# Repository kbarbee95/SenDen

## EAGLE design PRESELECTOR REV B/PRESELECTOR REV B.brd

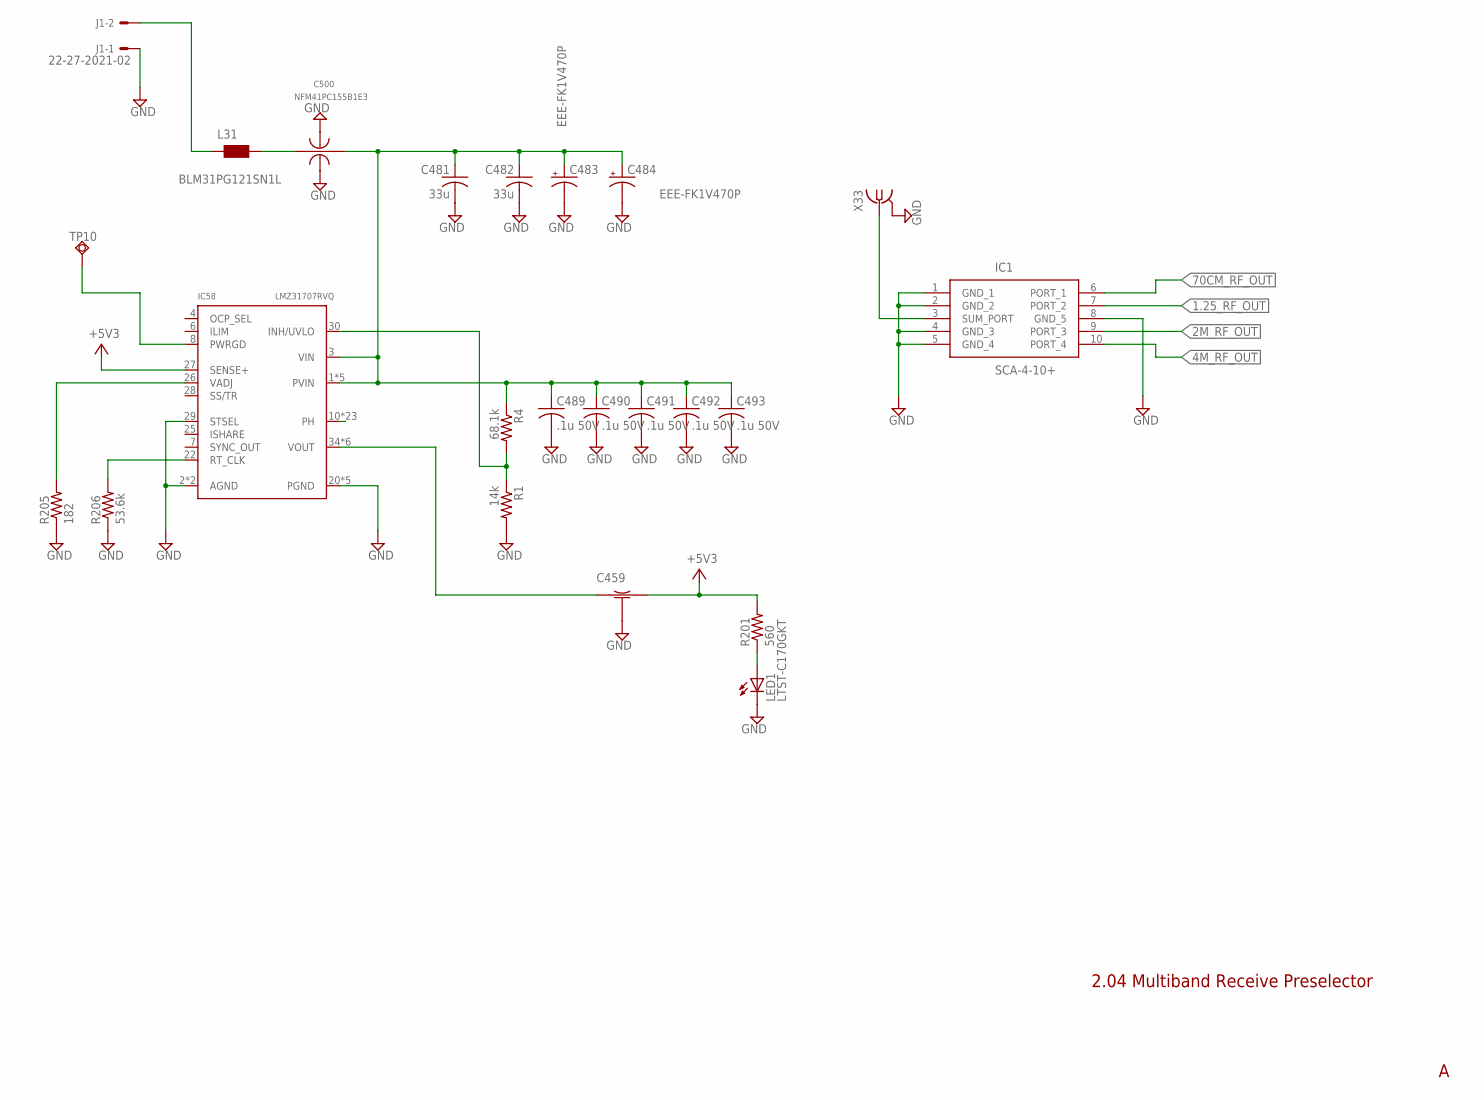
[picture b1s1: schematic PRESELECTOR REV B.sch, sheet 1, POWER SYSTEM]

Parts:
C459: NFM31PC276B0J3L; NFM31PC276
C481, C482: 33u; C1206K
C483, C484: EEE-FK1V470P; PANASONIC_D
C489, C490, C491, C492, C493: .1u 50V; C0603K
C500: NFM41PC155B1E3; NFM1806
IC1: SCA-4-10+
IC58: LMZ31707RVQ; RVQ
J1: 22-27-2021-02; 6410-02
L31: BLM31PG121SN1L; 1206
LED1: LTST-C170GKT; CHIPLED_0805
R1: 14k; R0603
R4: 68.1k; R0603
R201: 560; R0603
R205: 182; R0603
R206: 53.6k; R0603
TP10: TPSQB1,27; B1,27
X33: 0733660061; BU-SMA-V

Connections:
1.25_RF_OUT: IC1.7 (PORT_2); also elsewhere on the board
2M_RF_OUT: IC1.9 (PORT_3); also elsewhere on the board
4M_RF_OUT: IC1.10 (PORT_4); also elsewhere on the board
70CM_RF_OUT: IC1.6 (PORT_1); also elsewhere on the board
+5V3: C459.OUT, IC58.27 (SENSE+), R201.2; also elsewhere on the board
+13.8V_SW_FIL: C481.1, C482.1, C483.+, C484.+, C489.1, C490.1, C491.1, C492.1, C493.1, C500.2 (OUT), IC58.1 (PVIN), IC58.3 (VIN), IC58.11 (PVIN), IC58.12 (PVIN), IC58.39 (PVIN), IC58.40 (PVIN), R4.1
+13.8V_TPS: J1.2, L31.1
GND: C459.GND1 (GND), C459.GND2 (GND), C459.GND3 (GND), C459.GND4 (GND), C459.GND5 (GND), C481.2, C482.2, C483.-, C484.-, C489.2, C490.2, C491.2, C492.2, C493.2, C500.GND@1 (GND), C500.GND@2 (GND), IC1.1 (GND_1), IC1.2 (GND_2), IC1.4 (GND_3), IC1.5 (GND_4), IC1.8 (GND_5), IC58.2 (AGND), IC58.20 (PGND), IC58.21 (PGND), IC58.23 (AGND), IC58.29 (STSEL), IC58.31 (PGND), IC58.32 (PGND), IC58.33 (PGND), J1.1, LED1.C, R1.2, R205.1, R206.1, X33.2 (GND), X33.3 (GND), X33.4 (GND), X33.5 (GND); also elsewhere on the board
unnamed: C500.1 (IN), L31.2
unnamed: IC58.30 (INH/UVLO), R1.1, R4.2
unnamed: IC58.8 (PWRGD), TP10.TP
unnamed: IC58.22 (RT_CLK), R206.2
unnamed: IC58.26 (VADJ), R205.2
unnamed: C459.IN, IC58.34 (VOUT), IC58.35 (VOUT), IC58.36 (VOUT), IC58.37 (VOUT), IC58.38 (VOUT), IC58.41 (VOUT)
unnamed: LED1.A, R201.1
PH: IC58.10 (PH), IC58.13 (PH), IC58.14 (PH), IC58.15 (PH), IC58.16 (PH), IC58.17 (PH), IC58.18 (PH), IC58.19 (PH), IC58.42 (PH), IC58.42A (PH), IC58.42B (PH), IC58.42C (PH), IC58.42D (PH), IC58.42E (PH), IC58.42F (PH), IC58.42G (PH), IC58.42H (PH), IC58.42J (PH), IC58.42K (PH), IC58.42L (PH), IC58.42M (PH), IC58.42N (PH), IC58.42P (PH)
PRE_OUT: IC1.3 (SUM_PORT), X33.1

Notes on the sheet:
2.04 Multiband Receive Preselector

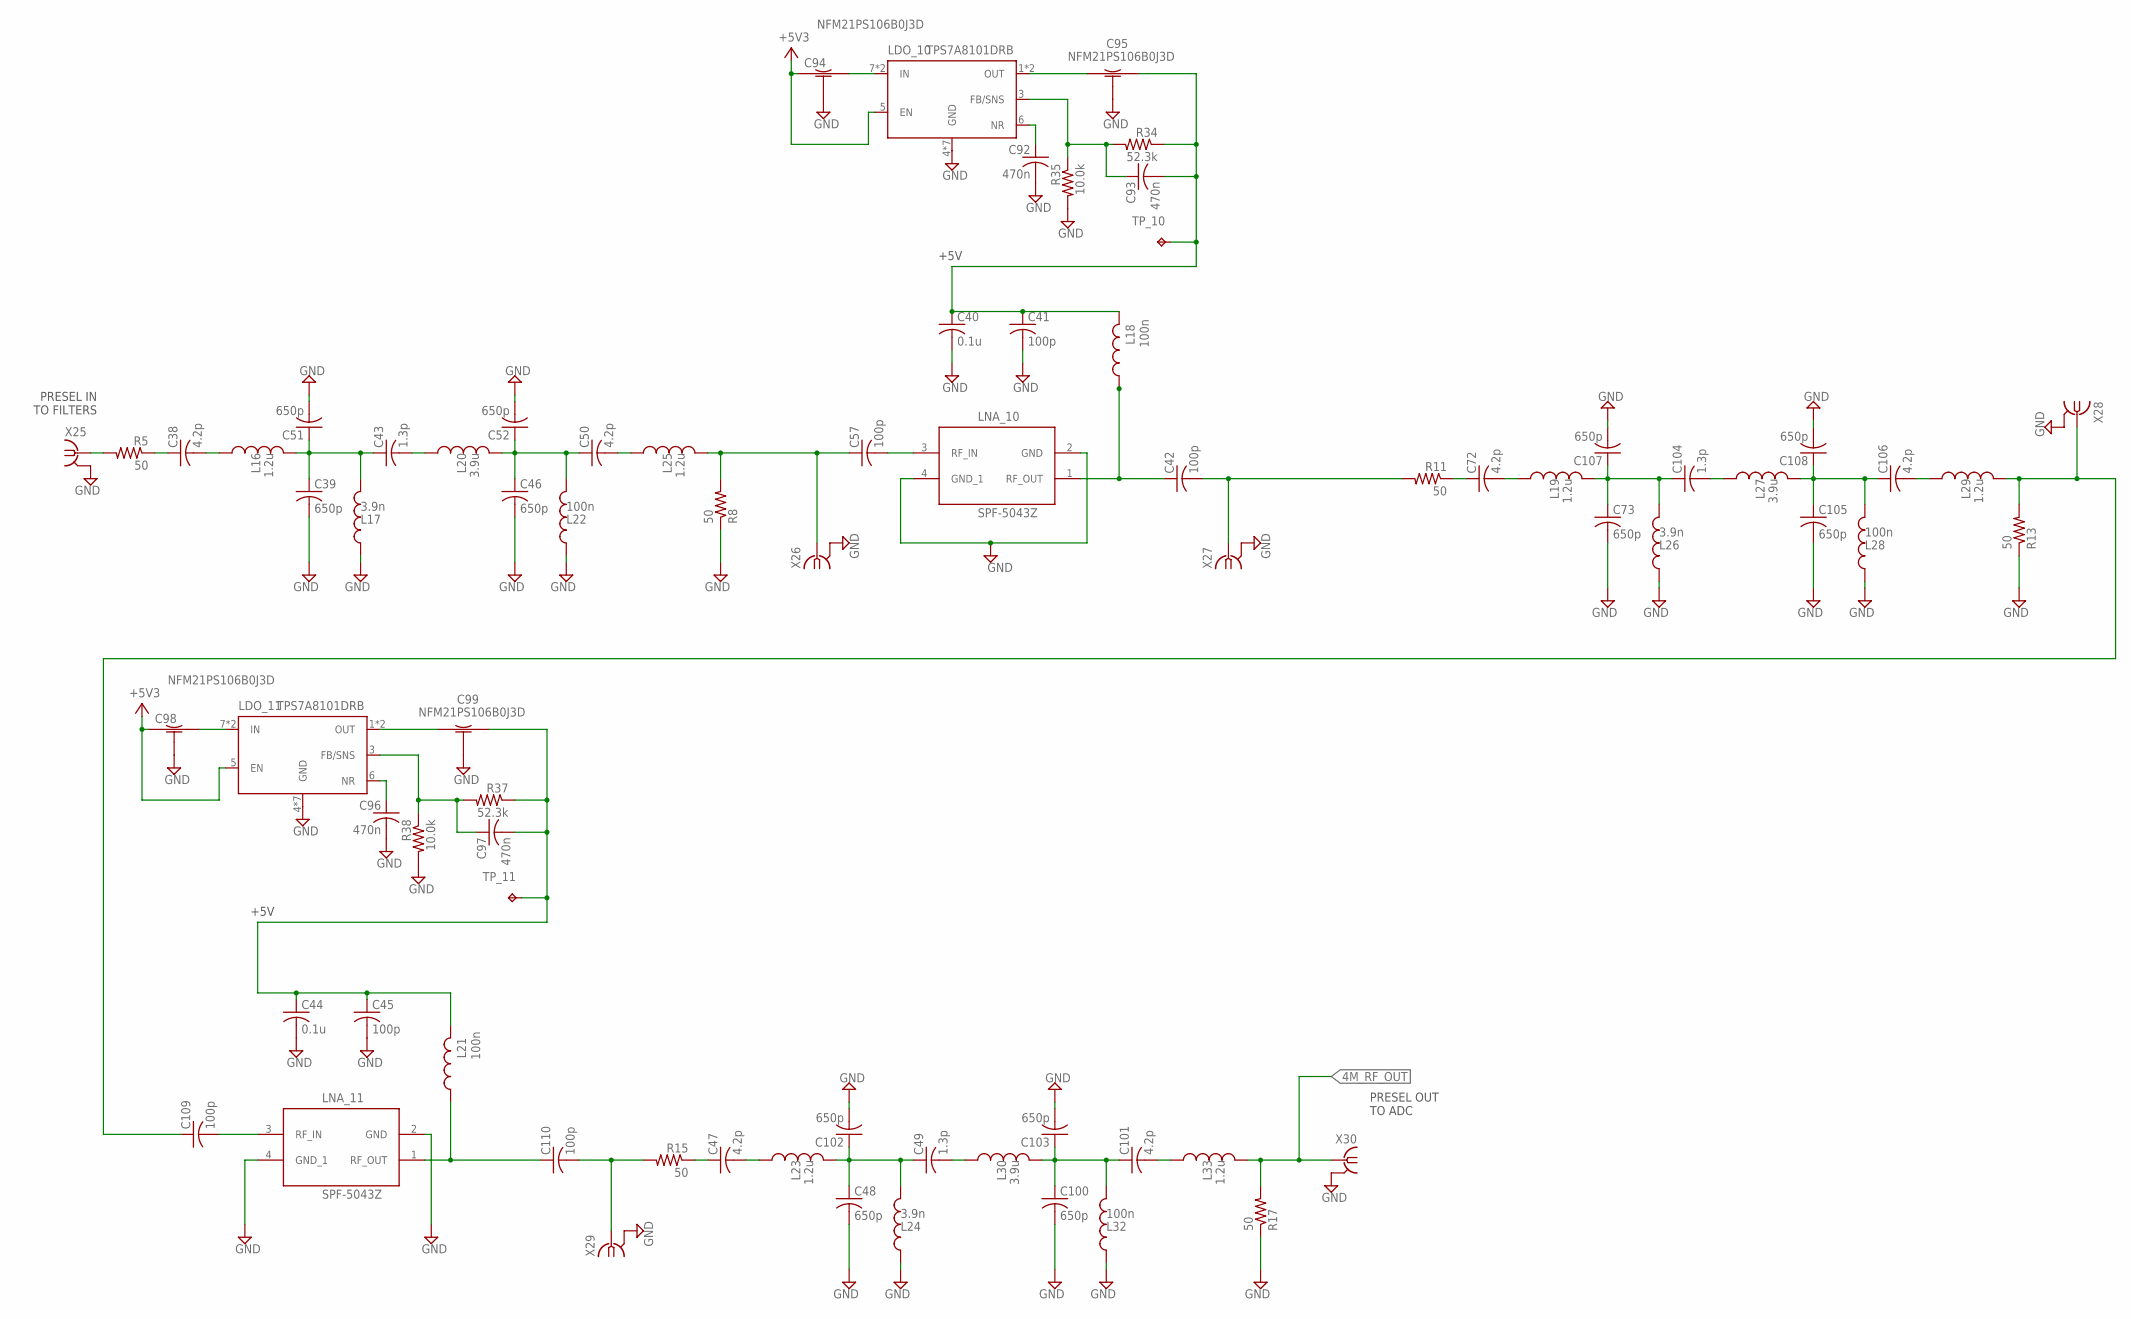
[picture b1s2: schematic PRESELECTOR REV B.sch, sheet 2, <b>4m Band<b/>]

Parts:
C38, C47, C50, C72, C101, C106: 4.2p; C0603K
C39, C46, C48, C51, C52, C73, C100, C102, C103, C105, C107, C108: 650p; C0603K
C40, C44: 0.1u; C0603K
C41, C42, C45, C57, C109, C110: 100p; C0603K
C43, C49, C104: 1.3p; C0603K
C92, C93, C96, C97: 470n; C0603K
C94, C95, C98, C99: NFM21PS106B0J3D; NFM21PS
L16, L19, L23, L25, L29, L33: 1.2u; C0603K
L17, L24, L26: 3.9n; C0603K
L18, L21: 100n; C1206
L20, L27, L30: 3.9u; C0603K
L22, L28, L32: 100n; C0603K
LDO_10, LDO_11: TPS7A8101DRB; DRB
LNA_10, LNA_11: SPF-5043Z
R5, R8, R11, R13, R15, R17: 50; R0603
R34, R37: 52.3k; R0603
R35, R38: 10.0k; R0603
TP_10, TP_11: TPTP20SQ; TP20SQ
X25, X26, X27, X28, X29, X30: 0733660061; BU-SMA-V

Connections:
4M_RF_OUT: L33.2, R17.2, X30.1; also elsewhere on the board
+5V3: C94.IN, C98.IN, LDO_10.5 (EN), LDO_11.5 (EN); also elsewhere on the board
GND: C39.2, C40.2, C41.2, C44.2, C45.2, C46.2, C48.2, C51.2, C52.2, C73.2, C92.2, C94.GND1 (GND), C94.GND2 (GND), C94.GND3 (GND), C94.GND4 (GND), C94.GND5 (GND), C94.GND6 (GND), C94.GND7 (GND), C94.GND8 (GND), C95.GND1 (GND), C95.GND2 (GND), C95.GND3 (GND), C95.GND4 (GND), C95.GND5 (GND), C95.GND6 (GND), C95.GND7 (GND), C95.GND8 (GND), C96.2, C98.GND1 (GND), C98.GND2 (GND), C98.GND3 (GND), C98.GND4 (GND), C98.GND5 (GND), C98.GND6 (GND), C98.GND7 (GND), C98.GND8 (GND), C99.GND1 (GND), C99.GND2 (GND), C99.GND3 (GND), C99.GND4 (GND), C99.GND5 (GND), C99.GND6 (GND), C99.GND7 (GND), C99.GND8 (GND), C100.2, C102.2, C103.2, C105.2, C107.2, C108.2, L17.1, L22.1, L24.1, L26.1, L28.1, L32.1, LDO_10.4 (GND), LDO_10.P1 (GND), LDO_10.P2 (GND), LDO_10.P3 (GND), LDO_10.P4 (GND), LDO_10.P5 (GND), LDO_10.PAD (GND), LDO_11.4 (GND), LDO_11.P1 (GND), LDO_11.P2 (GND), LDO_11.P3 (GND), LDO_11.P4 (GND), LDO_11.P5 (GND), LDO_11.PAD (GND), LNA_10.2 (GND), LNA_10.4 (GND_1), LNA_11.2 (GND), LNA_11.4 (GND_1), R8.1, R13.1, R17.1, R35.2, R38.2, X25.2 (GND), X25.3 (GND), X25.4 (GND), X25.5 (GND), X26.2 (GND), X26.3 (GND), X26.4 (GND), X26.5 (GND), X27.2 (GND), X27.3 (GND), X27.4 (GND), X27.5 (GND), X28.2 (GND), X28.3 (GND), X28.4 (GND), X28.5 (GND), X29.2 (GND), X29.3 (GND), X29.4 (GND), X29.5 (GND), X30.2 (GND), X30.3 (GND), X30.4 (GND), X30.5 (GND); also elsewhere on the board
LDO_10_5V: C40.1, C41.1, C93.2, C95.OUT, L18.2, R34.1, TP_10.TP
LDO_11_5V: C44.1, C45.1, C97.2, C99.OUT, L21.2, R37.1, TP_11.TP
LNA_10_IN: C57.1, L25.2, R8.2, X26.1
LNA_10_IN1: C109.1, L29.2, R13.2, X28.1
LNA_10_OUT: C42.1, L18.1, LNA_10.1 (RF_OUT)
LNA_11_OUT: C110.1, L21.1, LNA_11.1 (RF_OUT)
unnamed: R5.2, X25.1
unnamed: C38.1, R5.1
unnamed: C38.2, L16.1
unnamed: C39.1, C43.1, C51.1, L16.2, L17.2
unnamed: C43.2, L20.1
unnamed: C46.1, C50.1, C52.1, L20.2, L22.2
unnamed: C50.2, L25.1
unnamed: C57.2, LNA_10.3 (RF_IN)
unnamed: C93.1, LDO_10.3 (FB/SNS), R34.2, R35.1
unnamed: C92.1, LDO_10.6 (NR)
unnamed: C94.OUT, LDO_10.7 (IN), LDO_10.8 (IN)
unnamed: C95.IN, LDO_10.1 (OUT), LDO_10.2 (OUT)
unnamed: C72.1, R11.1
unnamed: C97.1, LDO_11.3 (FB/SNS), R37.2, R38.1
unnamed: C96.1, LDO_11.6 (NR)
unnamed: C98.OUT, LDO_11.7 (IN), LDO_11.8 (IN)
unnamed: C99.IN, LDO_11.1 (OUT), LDO_11.2 (OUT)
unnamed: C47.1, R15.1
unnamed: C47.2, L23.1
unnamed: C48.1, C49.1, C102.1, L23.2, L24.2
unnamed: C49.2, L30.1
unnamed: C72.2, L19.1
unnamed: C73.1, C104.1, C107.1, L19.2, L26.2
unnamed: C104.2, L27.1
unnamed: C105.1, C106.1, C108.1, L27.2, L28.2
unnamed: C106.2, L29.1
unnamed: C100.1, C101.1, C103.1, L30.2, L32.2
unnamed: C101.2, L33.1
unnamed: C109.2, LNA_11.3 (RF_IN)
unnamed: C110.2, R15.2, X29.1
SAW_14_IN: C42.2, R11.2, X27.1

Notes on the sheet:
PRESEL IN TO FILTERS
PRESEL OUT TO ADC
+5V

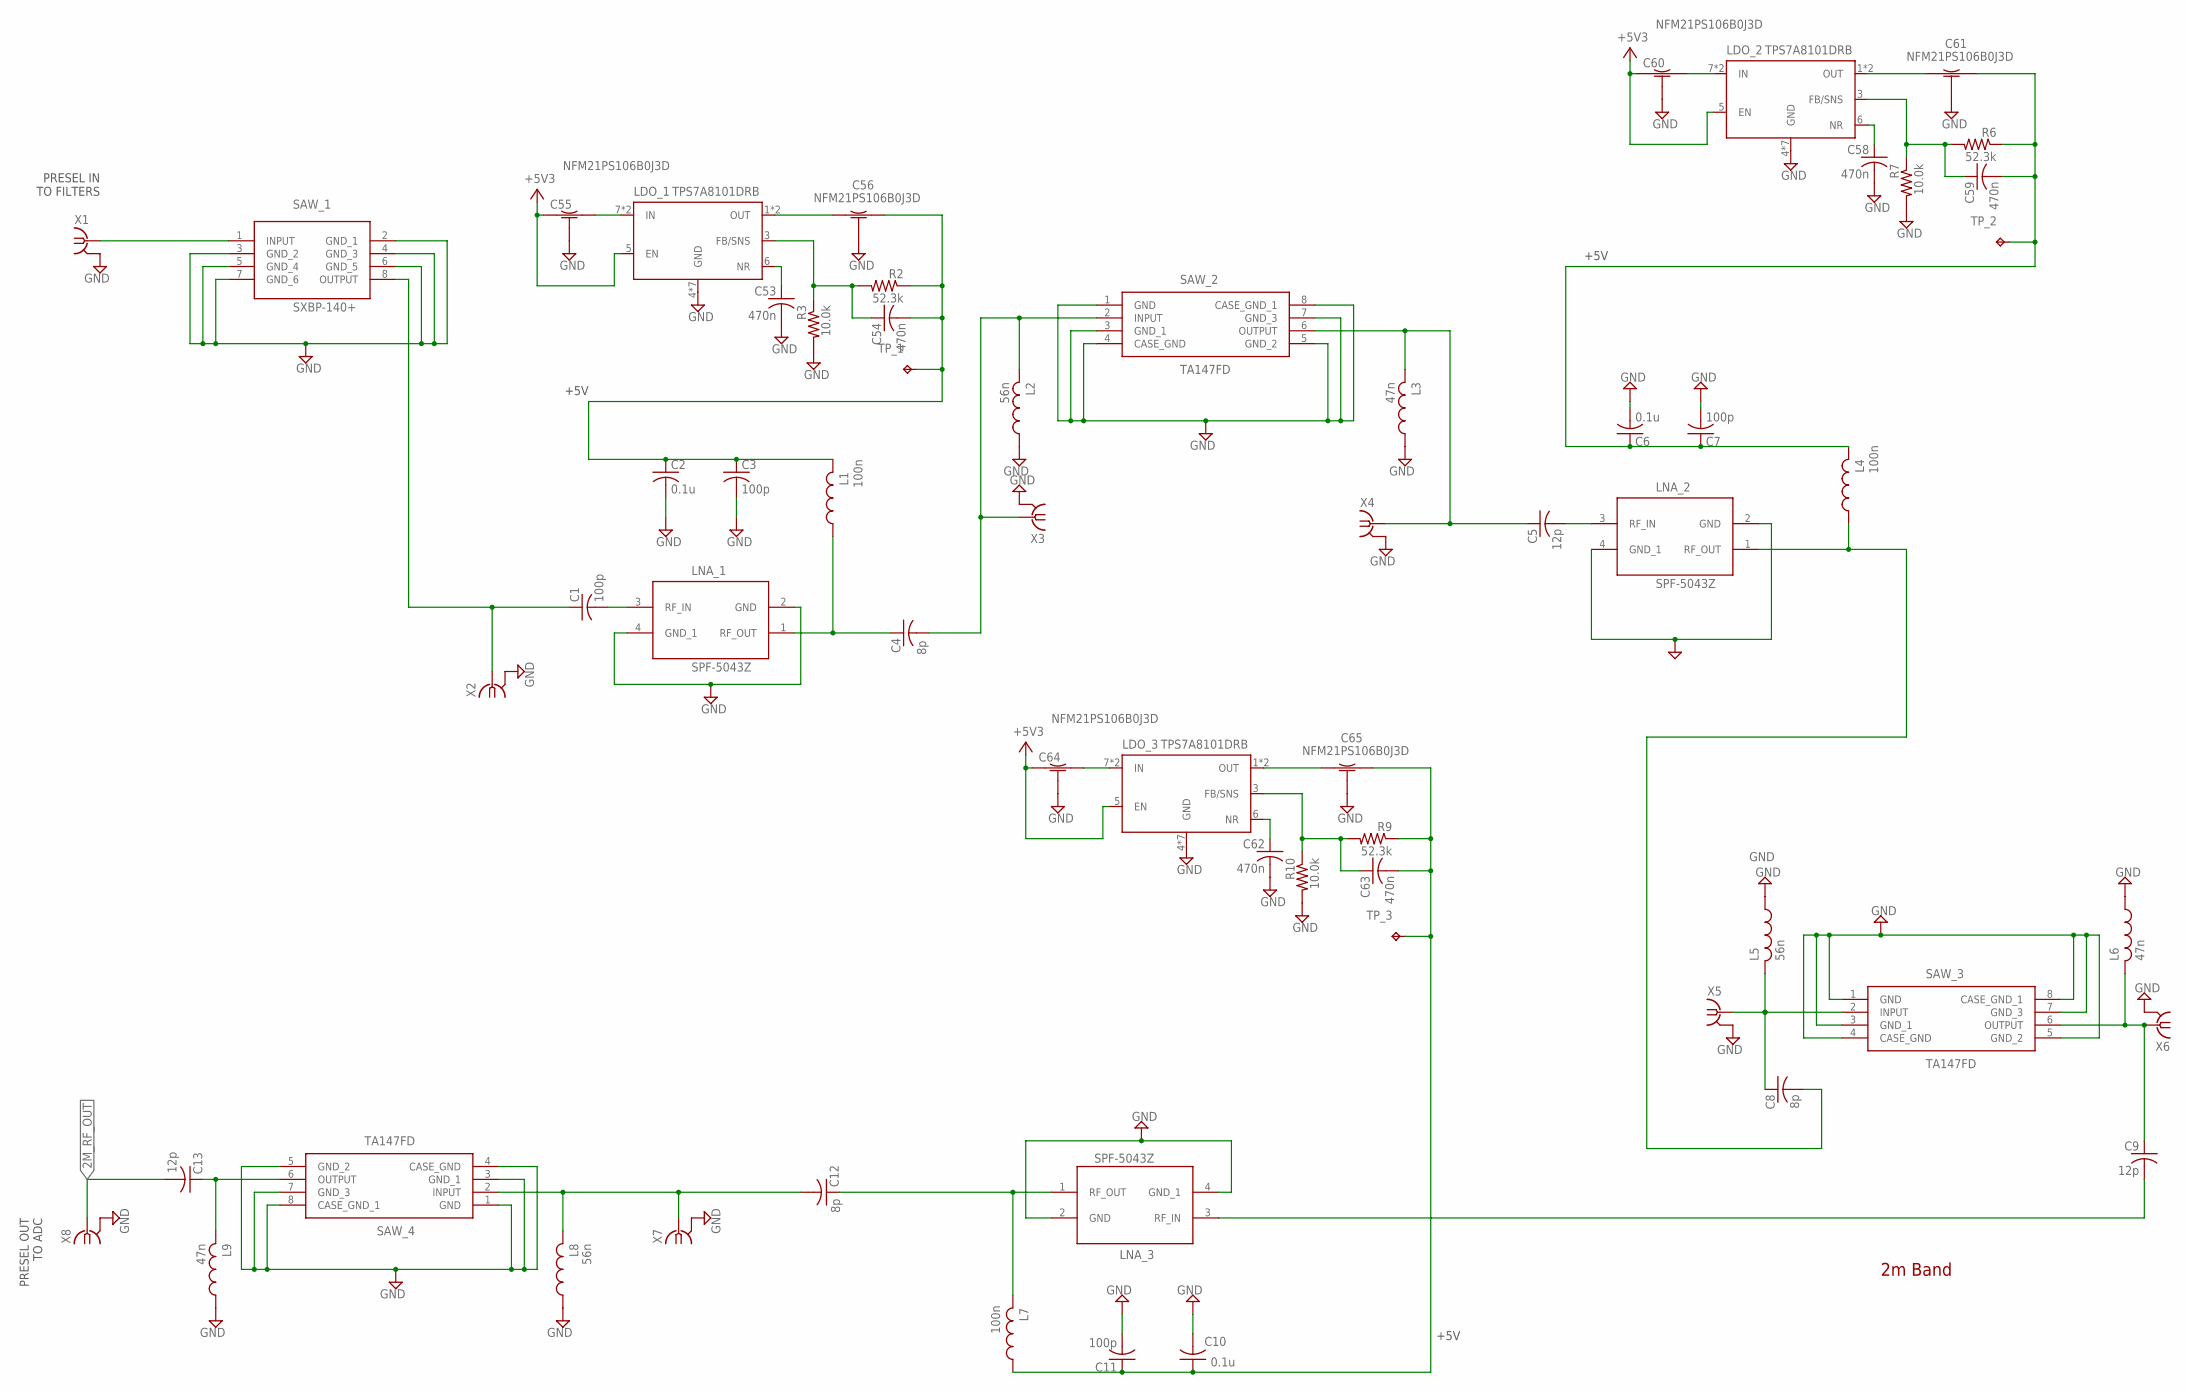
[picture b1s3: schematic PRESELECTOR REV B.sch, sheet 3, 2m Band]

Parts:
C1, C3, C7, C11: 100p; C0603K
C2, C6, C10: 0.1u; C0603K
C4, C8, C12: 8p; C0603K
C5, C9, C13: 12p; C0603K
C53, C54, C58, C59, C62, C63: 470n; C0603K
C55, C56, C60, C61, C64, C65: NFM21PS106B0J3D; NFM21PS
L1, L4, L7: 100n; C1206
L2, L5, L8: 56n; C1206
L3, L6, L9: 47n; C1206
LDO_1, LDO_2, LDO_3: TPS7A8101DRB; DRB
LNA_1, LNA_2, LNA_3: SPF-5043Z
R2, R6, R9: 52.3k; R0603
R3, R7, R10: 10.0k; R0603
SAW_1: SXBP-140+
SAW_2, SAW_3, SAW_4: TA147FD
TP_1, TP_2, TP_3: TPTP20SQ; TP20SQ
X1, X2, X3, X4, X5, X6, X7, X8: 0733660061; BU-SMA-V

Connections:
2M_RF_IN: SAW_1.1 (INPUT), X1.1
2M_RF_OUT: C13.2, X8.1; also elsewhere on the board
+5V3: C55.IN, C60.IN, C64.IN, LDO_1.5 (EN), LDO_2.5 (EN), LDO_3.5 (EN); also elsewhere on the board
GND: C2.2, C3.2, C6.2, C7.2, C10.2, C11.2, C53.2, C55.GND1 (GND), C55.GND2 (GND), C55.GND3 (GND), C55.GND4 (GND), C55.GND5 (GND), C55.GND6 (GND), C55.GND7 (GND), C55.GND8 (GND), C56.GND1 (GND), C56.GND2 (GND), C56.GND3 (GND), C56.GND4 (GND), C56.GND5 (GND), C56.GND6 (GND), C56.GND7 (GND), C56.GND8 (GND), C58.2, C60.GND1 (GND), C60.GND2 (GND), C60.GND3 (GND), C60.GND4 (GND), C60.GND5 (GND), C60.GND6 (GND), C60.GND7 (GND), C60.GND8 (GND), C61.GND1 (GND), C61.GND2 (GND), C61.GND3 (GND), C61.GND4 (GND), C61.GND5 (GND), C61.GND6 (GND), C61.GND7 (GND), C61.GND8 (GND), C62.2, C64.GND1 (GND), C64.GND2 (GND), C64.GND3 (GND), C64.GND4 (GND), C64.GND5 (GND), C64.GND6 (GND), C64.GND7 (GND), C64.GND8 (GND), C65.GND1 (GND), C65.GND2 (GND), C65.GND3 (GND), C65.GND4 (GND), C65.GND5 (GND), C65.GND6 (GND), C65.GND7 (GND), C65.GND8 (GND), L2.1, L3.1, L5.1, L6.1, L8.1, L9.1, LDO_1.4 (GND), LDO_1.P1 (GND), LDO_1.P2 (GND), LDO_1.P3 (GND), LDO_1.P4 (GND), LDO_1.P5 (GND), LDO_1.PAD (GND), LDO_2.4 (GND), LDO_2.P1 (GND), LDO_2.P2 (GND), LDO_2.P3 (GND), LDO_2.P4 (GND), LDO_2.P5 (GND), LDO_2.PAD (GND), LDO_3.4 (GND), LDO_3.P1 (GND), LDO_3.P2 (GND), LDO_3.P3 (GND), LDO_3.P4 (GND), LDO_3.P5 (GND), LDO_3.PAD (GND), LNA_1.2 (GND), LNA_1.4 (GND_1), LNA_2.2 (GND), LNA_2.4 (GND_1), LNA_3.2 (GND), LNA_3.4 (GND_1), R3.2, R7.2, R10.2, SAW_1.2 (GND_1), SAW_1.3 (GND_2), SAW_1.4 (GND_3), SAW_1.5 (GND_4), SAW_1.6 (GND_5), SAW_1.7 (GND_6), SAW_2.1 (GND), SAW_2.3 (GND_1), SAW_2.4 (CASE_GND), SAW_2.5 (GND_2), SAW_2.7 (GND_3), SAW_2.8 (CASE_GND_1), SAW_3.1 (GND), SAW_3.3 (GND_1), SAW_3.4 (CASE_GND), SAW_3.5 (GND_2), SAW_3.7 (GND_3), SAW_3.8 (CASE_GND_1), SAW_4.1 (GND), SAW_4.3 (GND_1), SAW_4.4 (CASE_GND), SAW_4.5 (GND_2), SAW_4.7 (GND_3), SAW_4.8 (CASE_GND_1), X1.2 (GND), X1.3 (GND), X1.4 (GND), X1.5 (GND), X2.2 (GND), X2.3 (GND), X2.4 (GND), X2.5 (GND), X3.2 (GND), X3.3 (GND), X3.4 (GND), X3.5 (GND), X4.2 (GND), X4.3 (GND), X4.4 (GND), X4.5 (GND), X5.2 (GND), X5.3 (GND), X5.4 (GND), X5.5 (GND), X6.2 (GND), X6.3 (GND), X6.4 (GND), X6.5 (GND), X7.2 (GND), X7.3 (GND), X7.4 (GND), X7.5 (GND), X8.2 (GND), X8.3 (GND), X8.4 (GND), X8.5 (GND); also elsewhere on the board
LDO_1_5V: C2.1, C3.1, C54.2, C56.OUT, L1.2, R2.1, TP_1.TP
LDO_2_5V: C6.1, C7.1, C59.2, C61.OUT, L4.2, R6.1, TP_2.TP
LDO_3_5V: C10.1, C11.1, C63.2, C65.OUT, L7.1, R9.1, TP_3.TP
LNA_1_IN: C1.2, LNA_1.3 (RF_IN)
LNA_1_OUT: C4.1, L1.1, LNA_1.1 (RF_OUT)
LNA_2_IN: C5.2, LNA_2.3 (RF_IN)
LNA_2_OUT: C8.2, L4.1, LNA_2.1 (RF_OUT)
LNA_3_IN: C9.2, LNA_3.3 (RF_IN)
LNA_3_OUT: C12.1, L7.2, LNA_3.1 (RF_OUT)
unnamed: C54.1, LDO_1.3 (FB/SNS), R2.2, R3.1
unnamed: C53.1, LDO_1.6 (NR)
unnamed: C55.OUT, LDO_1.7 (IN), LDO_1.8 (IN)
unnamed: C56.IN, LDO_1.1 (OUT), LDO_1.2 (OUT)
unnamed: C59.1, LDO_2.3 (FB/SNS), R6.2, R7.1
unnamed: C58.1, LDO_2.6 (NR)
unnamed: C60.OUT, LDO_2.7 (IN), LDO_2.8 (IN)
unnamed: C61.IN, LDO_2.1 (OUT), LDO_2.2 (OUT)
unnamed: C63.1, LDO_3.3 (FB/SNS), R9.2, R10.1
unnamed: C62.1, LDO_3.6 (NR)
unnamed: C64.OUT, LDO_3.7 (IN), LDO_3.8 (IN)
unnamed: C65.IN, LDO_3.1 (OUT), LDO_3.2 (OUT)
SAW_1_OUT: C1.1, SAW_1.8 (OUTPUT), X2.1
SAW_2_IN: C4.2, L2.2, SAW_2.2 (INPUT), X3.1
SAW_2_OUT: C5.1, L3.2, SAW_2.6 (OUTPUT), X4.1
SAW_3_IN: C8.1, L5.2, SAW_3.2 (INPUT), X5.1
SAW_3_OUT: C9.1, L6.2, SAW_3.6 (OUTPUT), X6.1
SAW_4_IN: C12.2, L8.2, SAW_4.2 (INPUT), X7.1
SAW_4_OUT: C13.1, L9.2, SAW_4.6 (OUTPUT)

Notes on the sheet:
PRESEL IN TO FILTERS
PRESEL OUT TO ADC
2m Band
+5V

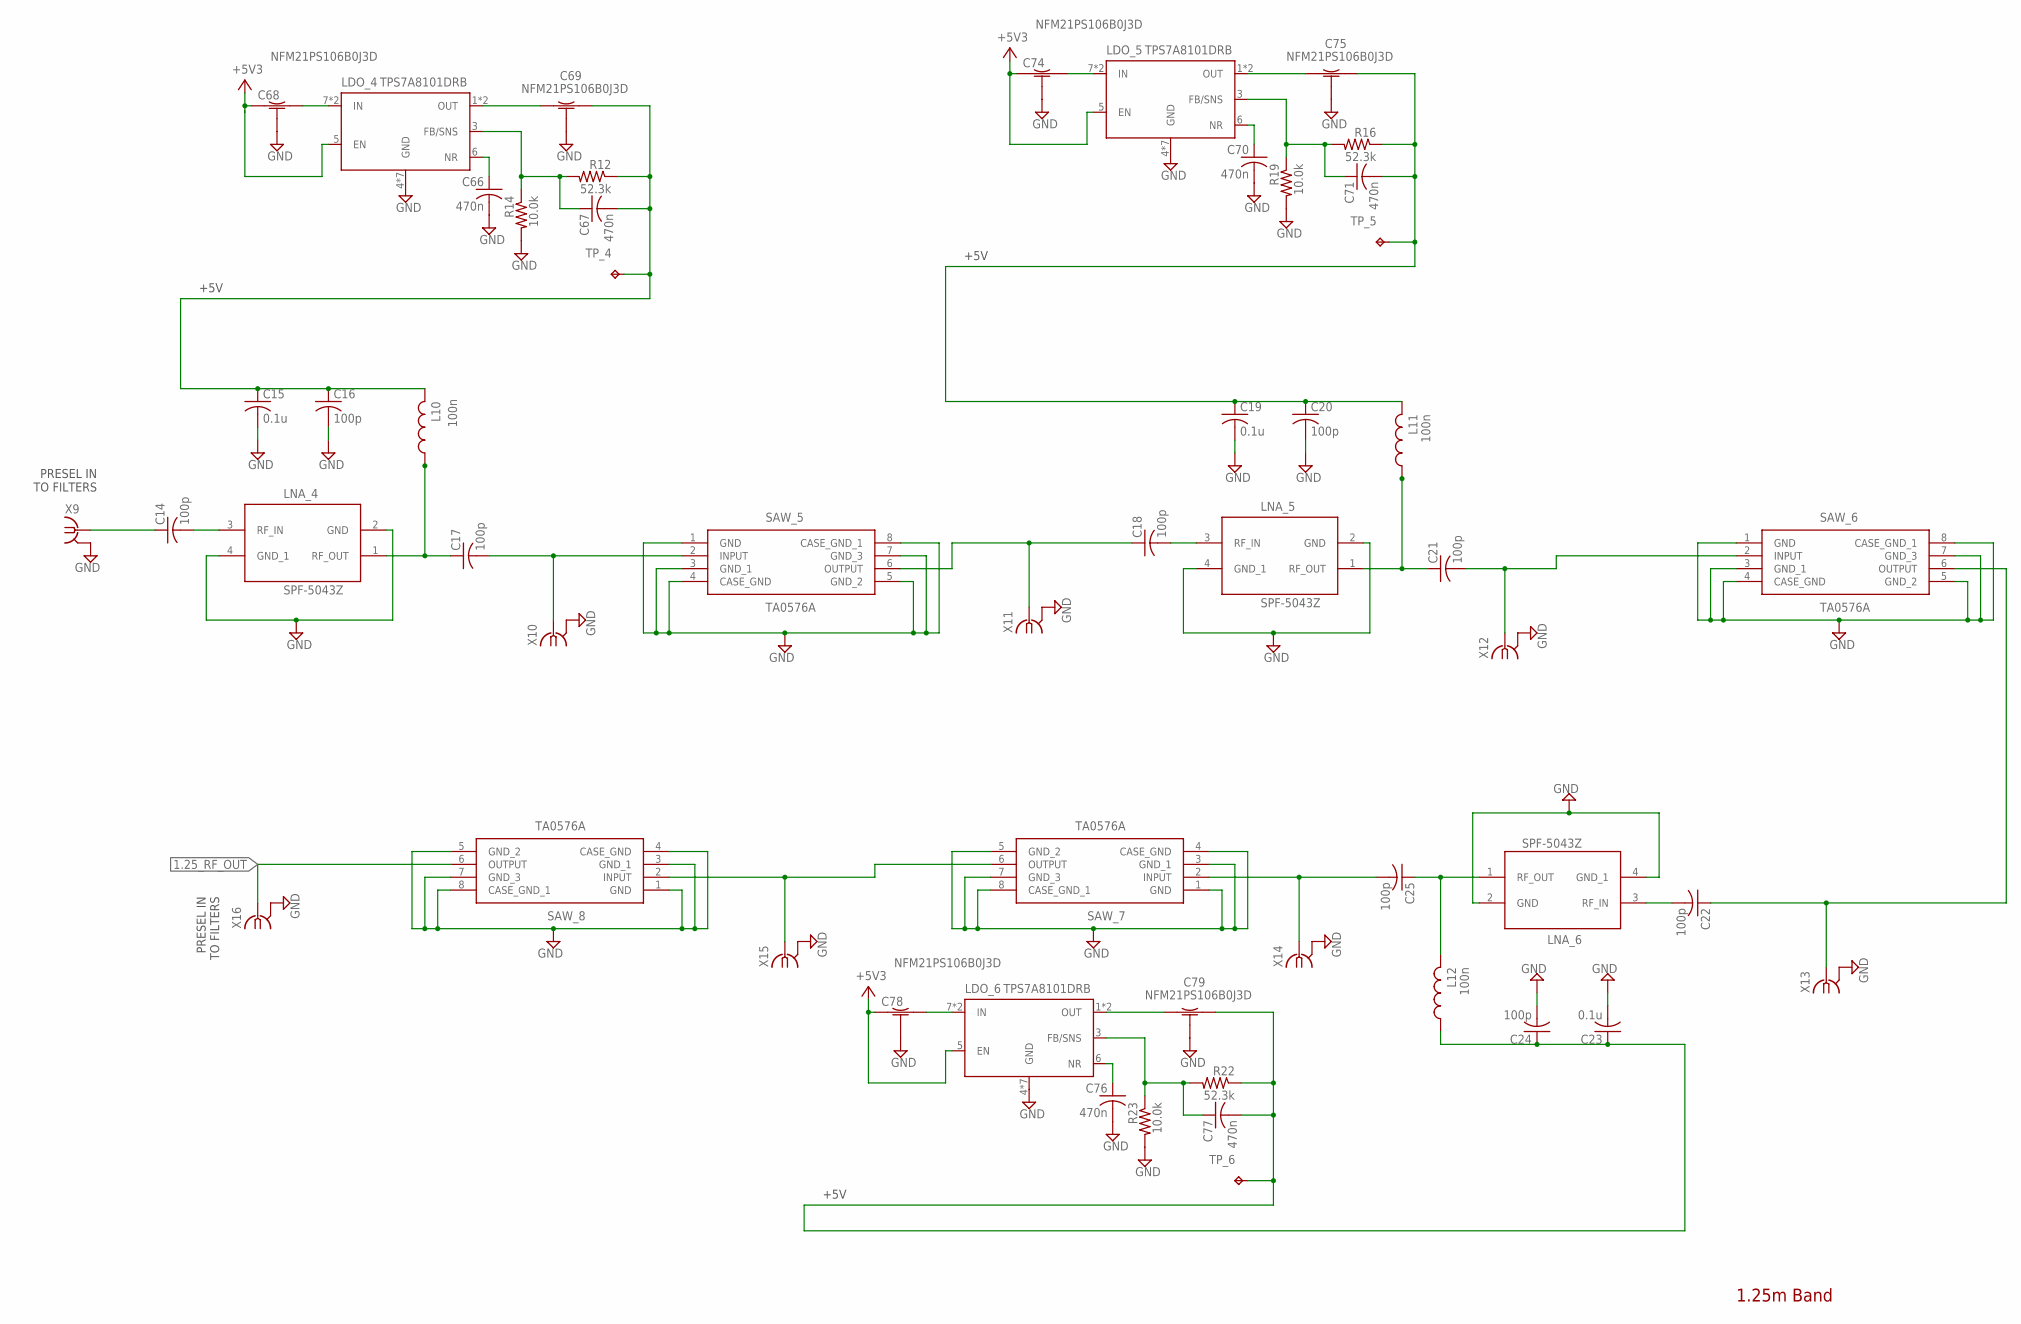
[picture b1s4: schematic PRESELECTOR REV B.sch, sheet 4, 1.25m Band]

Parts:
C14, C16, C17, C18, C20, C21, C22, C24, C25: 100p; C0603K
C15, C19, C23: 0.1u; C0603K
C66, C67, C70, C71, C76, C77: 470n; C0603K
C68, C69, C74, C75, C78, C79: NFM21PS106B0J3D; NFM21PS
L10, L11, L12: 100n; C1206
LDO_4, LDO_5, LDO_6: TPS7A8101DRB; DRB
LNA_4, LNA_5, LNA_6: SPF-5043Z
R12, R16, R22: 52.3k; R0603
R14, R19, R23: 10.0k; R0603
SAW_5, SAW_6, SAW_7, SAW_8: TA0576A
TP_4, TP_5, TP_6: TPTP20SQ; TP20SQ
X9, X10, X11, X12, X13, X14, X15, X16: 0733660061; BU-SMA-V

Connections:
1.25M_RF_IN: C14.1, X9.1
1.25_RF_OUT: SAW_8.6 (OUTPUT), X16.1; also elsewhere on the board
+5V3: C68.IN, C74.IN, C78.IN, LDO_4.5 (EN), LDO_5.5 (EN), LDO_6.5 (EN); also elsewhere on the board
GND: C15.2, C16.2, C19.2, C20.2, C23.2, C24.2, C66.2, C68.GND1 (GND), C68.GND2 (GND), C68.GND3 (GND), C68.GND4 (GND), C68.GND5 (GND), C68.GND6 (GND), C68.GND7 (GND), C68.GND8 (GND), C69.GND1 (GND), C69.GND2 (GND), C69.GND3 (GND), C69.GND4 (GND), C69.GND5 (GND), C69.GND6 (GND), C69.GND7 (GND), C69.GND8 (GND), C70.2, C74.GND1 (GND), C74.GND2 (GND), C74.GND3 (GND), C74.GND4 (GND), C74.GND5 (GND), C74.GND6 (GND), C74.GND7 (GND), C74.GND8 (GND), C75.GND1 (GND), C75.GND2 (GND), C75.GND3 (GND), C75.GND4 (GND), C75.GND5 (GND), C75.GND6 (GND), C75.GND7 (GND), C75.GND8 (GND), C76.2, C78.GND1 (GND), C78.GND2 (GND), C78.GND3 (GND), C78.GND4 (GND), C78.GND5 (GND), C78.GND6 (GND), C78.GND7 (GND), C78.GND8 (GND), C79.GND1 (GND), C79.GND2 (GND), C79.GND3 (GND), C79.GND4 (GND), C79.GND5 (GND), C79.GND6 (GND), C79.GND7 (GND), C79.GND8 (GND), LDO_4.4 (GND), LDO_4.P1 (GND), LDO_4.P2 (GND), LDO_4.P3 (GND), LDO_4.P4 (GND), LDO_4.P5 (GND), LDO_4.PAD (GND), LDO_5.4 (GND), LDO_5.P1 (GND), LDO_5.P2 (GND), LDO_5.P3 (GND), LDO_5.P4 (GND), LDO_5.P5 (GND), LDO_5.PAD (GND), LDO_6.4 (GND), LDO_6.P1 (GND), LDO_6.P2 (GND), LDO_6.P3 (GND), LDO_6.P4 (GND), LDO_6.P5 (GND), LDO_6.PAD (GND), LNA_4.2 (GND), LNA_4.4 (GND_1), LNA_5.2 (GND), LNA_5.4 (GND_1), LNA_6.2 (GND), LNA_6.4 (GND_1), R14.2, R19.2, R23.2, SAW_5.1 (GND), SAW_5.3 (GND_1), SAW_5.4 (CASE_GND), SAW_5.5 (GND_2), SAW_5.7 (GND_3), SAW_5.8 (CASE_GND_1), SAW_6.1 (GND), SAW_6.3 (GND_1), SAW_6.4 (CASE_GND), SAW_6.5 (GND_2), SAW_6.7 (GND_3), SAW_6.8 (CASE_GND_1), SAW_7.1 (GND), SAW_7.3 (GND_1), SAW_7.4 (CASE_GND), SAW_7.5 (GND_2), SAW_7.7 (GND_3), SAW_7.8 (CASE_GND_1), SAW_8.1 (GND), SAW_8.3 (GND_1), SAW_8.4 (CASE_GND), SAW_8.5 (GND_2), SAW_8.7 (GND_3), SAW_8.8 (CASE_GND_1), X9.2 (GND), X9.3 (GND), X9.4 (GND), X9.5 (GND), X10.2 (GND), X10.3 (GND), X10.4 (GND), X10.5 (GND), X11.2 (GND), X11.3 (GND), X11.4 (GND), X11.5 (GND), X12.2 (GND), X12.3 (GND), X12.4 (GND), X12.5 (GND), X13.2 (GND), X13.3 (GND), X13.4 (GND), X13.5 (GND), X14.2 (GND), X14.3 (GND), X14.4 (GND), X14.5 (GND), X15.2 (GND), X15.3 (GND), X15.4 (GND), X15.5 (GND), X16.2 (GND), X16.3 (GND), X16.4 (GND), X16.5 (GND); also elsewhere on the board
LDO_4_5V: C15.1, C16.1, C67.2, C69.OUT, L10.2, R12.1, TP_4.TP
LDO_5_5V: C19.1, C20.1, C71.2, C75.OUT, L11.2, R16.1, TP_5.TP
LDO_6_5V: C23.1, C24.1, C77.2, C79.OUT, L12.1, R22.1, TP_6.TP
LNA_4_IN: C14.2, LNA_4.3 (RF_IN)
LNA_4_OUT: C17.1, L10.1, LNA_4.1 (RF_OUT)
LNA_5_IN: C18.2, LNA_5.3 (RF_IN)
LNA_5_OUT: C21.1, L11.1, LNA_5.1 (RF_OUT)
LNA_6_IN: C22.2, LNA_6.3 (RF_IN)
LNA_6_OUT: C25.1, L12.2, LNA_6.1 (RF_OUT)
unnamed: C67.1, LDO_4.3 (FB/SNS), R12.2, R14.1
unnamed: C66.1, LDO_4.6 (NR)
unnamed: C68.OUT, LDO_4.7 (IN), LDO_4.8 (IN)
unnamed: C69.IN, LDO_4.1 (OUT), LDO_4.2 (OUT)
unnamed: C71.1, LDO_5.3 (FB/SNS), R16.2, R19.1
unnamed: C70.1, LDO_5.6 (NR)
unnamed: C74.OUT, LDO_5.7 (IN), LDO_5.8 (IN)
unnamed: C75.IN, LDO_5.1 (OUT), LDO_5.2 (OUT)
unnamed: C77.1, LDO_6.3 (FB/SNS), R22.2, R23.1
unnamed: C76.1, LDO_6.6 (NR)
unnamed: C78.OUT, LDO_6.7 (IN), LDO_6.8 (IN)
unnamed: C79.IN, LDO_6.1 (OUT), LDO_6.2 (OUT)
SAW+6_OUT: C22.1, SAW_6.6 (OUTPUT), X13.1
SAW_5_IN: C17.2, SAW_5.2 (INPUT), X10.1
SAW_5_OUT: C18.1, SAW_5.6 (OUTPUT), X11.1
SAW_6_IN: C21.2, SAW_6.2 (INPUT), X12.1
SAW_7_8_RF: SAW_7.6 (OUTPUT), SAW_8.2 (INPUT), X15.1
SAW_7_IN: C25.2, SAW_7.2 (INPUT), X14.1

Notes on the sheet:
PRESEL IN TO FILTERS
1.25m Band
+5V

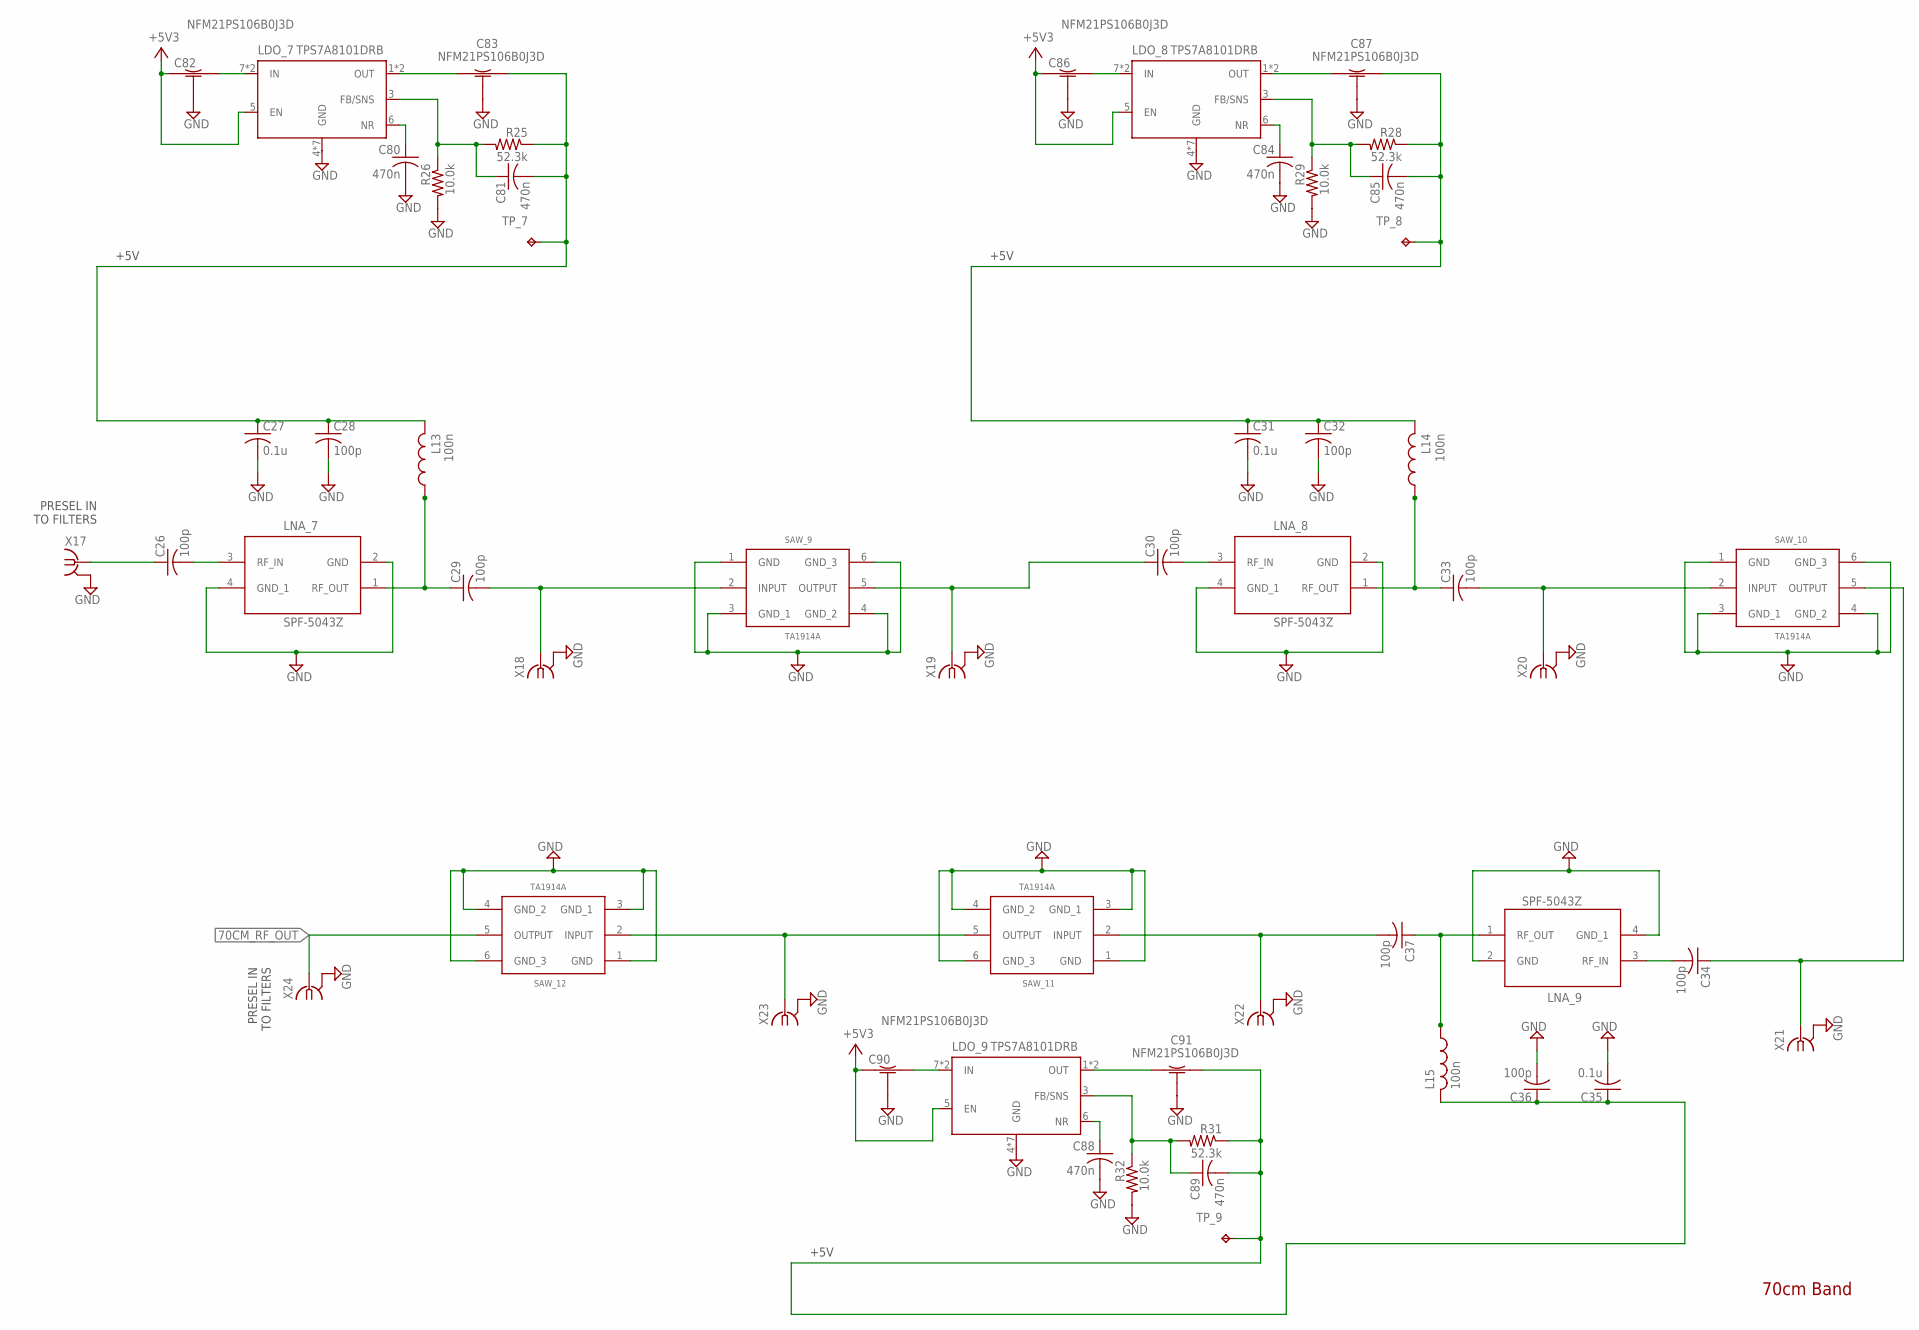
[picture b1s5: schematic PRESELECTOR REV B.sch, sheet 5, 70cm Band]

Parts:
C26, C28, C29, C30, C32, C33, C34, C36, C37: 100p; C0603K
C27, C31, C35: 0.1u; C0603K
C80, C81, C84, C85, C88, C89: 470n; C0603K
C82, C83, C86, C87, C90, C91: NFM21PS106B0J3D; NFM21PS
L13, L14, L15: 100n; C1206
LDO_7, LDO_8, LDO_9: TPS7A8101DRB; DRB
LNA_7, LNA_8, LNA_9: SPF-5043Z
R25, R28, R31: 52.3k; R0603
R26, R29, R32: 10.0k; R0603
SAW_9, SAW_10, SAW_11, SAW_12: TA1914A
TP_7, TP_8, TP_9: TPTP20SQ; TP20SQ
X17, X18, X19, X20, X21, X22, X23, X24: 0733660061; BU-SMA-V

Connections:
70CM_RF_IN: C26.1, X17.1
70CM_RF_OUT: SAW_12.5 (OUTPUT), X24.1; also elsewhere on the board
+5V3: C82.IN, C86.IN, C90.IN, LDO_7.5 (EN), LDO_8.5 (EN), LDO_9.5 (EN); also elsewhere on the board
GND: C27.2, C28.2, C31.2, C32.2, C35.2, C36.2, C80.2, C82.GND1 (GND), C82.GND2 (GND), C82.GND3 (GND), C82.GND4 (GND), C82.GND5 (GND), C82.GND6 (GND), C82.GND7 (GND), C82.GND8 (GND), C83.GND1 (GND), C83.GND2 (GND), C83.GND3 (GND), C83.GND4 (GND), C83.GND5 (GND), C83.GND6 (GND), C83.GND7 (GND), C83.GND8 (GND), C84.2, C86.GND1 (GND), C86.GND2 (GND), C86.GND3 (GND), C86.GND4 (GND), C86.GND5 (GND), C86.GND6 (GND), C86.GND7 (GND), C86.GND8 (GND), C87.GND1 (GND), C87.GND2 (GND), C87.GND3 (GND), C87.GND4 (GND), C87.GND5 (GND), C87.GND6 (GND), C87.GND7 (GND), C87.GND8 (GND), C88.2, C90.GND1 (GND), C90.GND2 (GND), C90.GND3 (GND), C90.GND4 (GND), C90.GND5 (GND), C90.GND6 (GND), C90.GND7 (GND), C90.GND8 (GND), C91.GND1 (GND), C91.GND2 (GND), C91.GND3 (GND), C91.GND4 (GND), C91.GND5 (GND), C91.GND6 (GND), C91.GND7 (GND), C91.GND8 (GND), LDO_7.4 (GND), LDO_7.P1 (GND), LDO_7.P2 (GND), LDO_7.P3 (GND), LDO_7.P4 (GND), LDO_7.P5 (GND), LDO_7.PAD (GND), LDO_8.4 (GND), LDO_8.P1 (GND), LDO_8.P2 (GND), LDO_8.P3 (GND), LDO_8.P4 (GND), LDO_8.P5 (GND), LDO_8.PAD (GND), LDO_9.4 (GND), LDO_9.P1 (GND), LDO_9.P2 (GND), LDO_9.P3 (GND), LDO_9.P4 (GND), LDO_9.P5 (GND), LDO_9.PAD (GND), LNA_7.2 (GND), LNA_7.4 (GND_1), LNA_8.2 (GND), LNA_8.4 (GND_1), LNA_9.2 (GND), LNA_9.4 (GND_1), R26.2, R29.2, R32.2, SAW_9.1 (GND), SAW_9.3 (GND_1), SAW_9.4 (GND_2), SAW_9.6 (GND_3), SAW_10.1 (GND), SAW_10.3 (GND_1), SAW_10.4 (GND_2), SAW_10.6 (GND_3), SAW_11.1 (GND), SAW_11.3 (GND_1), SAW_11.4 (GND_2), SAW_11.6 (GND_3), SAW_12.1 (GND), SAW_12.3 (GND_1), SAW_12.4 (GND_2), SAW_12.6 (GND_3), X17.2 (GND), X17.3 (GND), X17.4 (GND), X17.5 (GND), X18.2 (GND), X18.3 (GND), X18.4 (GND), X18.5 (GND), X19.2 (GND), X19.3 (GND), X19.4 (GND), X19.5 (GND), X20.2 (GND), X20.3 (GND), X20.4 (GND), X20.5 (GND), X21.2 (GND), X21.3 (GND), X21.4 (GND), X21.5 (GND), X22.2 (GND), X22.3 (GND), X22.4 (GND), X22.5 (GND), X23.2 (GND), X23.3 (GND), X23.4 (GND), X23.5 (GND), X24.2 (GND), X24.3 (GND), X24.4 (GND), X24.5 (GND); also elsewhere on the board
LDO_7_5V: C27.1, C28.1, C81.2, C83.OUT, L13.2, R25.1, TP_7.TP
LDO_8_5V: C31.1, C32.1, C85.2, C87.OUT, L14.2, R28.1, TP_8.TP
LDO_9_5V: C35.1, C36.1, C89.2, C91.OUT, L15.2, R31.1, TP_9.TP
LNA_7_IN: C26.2, LNA_7.3 (RF_IN)
LNA_7_OUT: C29.1, L13.1, LNA_7.1 (RF_OUT)
LNA_8_IN: C30.2, LNA_8.3 (RF_IN)
LNA_8_OUT: C33.1, L14.1, LNA_8.1 (RF_OUT)
LNA_9_IN: C34.2, LNA_9.3 (RF_IN)
LNA_9_OUT: C37.1, L15.1, LNA_9.1 (RF_OUT)
unnamed: C81.1, LDO_7.3 (FB/SNS), R25.2, R26.1
unnamed: C80.1, LDO_7.6 (NR)
unnamed: C82.OUT, LDO_7.7 (IN), LDO_7.8 (IN)
unnamed: C83.IN, LDO_7.1 (OUT), LDO_7.2 (OUT)
unnamed: C85.1, LDO_8.3 (FB/SNS), R28.2, R29.1
unnamed: C84.1, LDO_8.6 (NR)
unnamed: C86.OUT, LDO_8.7 (IN), LDO_8.8 (IN)
unnamed: C87.IN, LDO_8.1 (OUT), LDO_8.2 (OUT)
unnamed: C89.1, LDO_9.3 (FB/SNS), R31.2, R32.1
unnamed: C88.1, LDO_9.6 (NR)
unnamed: C90.OUT, LDO_9.7 (IN), LDO_9.8 (IN)
unnamed: C91.IN, LDO_9.1 (OUT), LDO_9.2 (OUT)
SAW_9_IN: C29.2, SAW_9.2 (INPUT), X18.1
SAW_9_OUT: C30.1, SAW_9.5 (OUTPUT), X19.1
SAW_10_IN: C33.2, SAW_10.2 (INPUT), X20.1
SAW_10_OUT: C34.1, SAW_10.5 (OUTPUT), X21.1
SAW_11_12_RF: SAW_11.5 (OUTPUT), SAW_12.2 (INPUT), X23.1
SAW_11_IN: C37.2, SAW_11.2 (INPUT), X22.1

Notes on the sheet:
PRESEL IN TO FILTERS
70cm Band
+5V
